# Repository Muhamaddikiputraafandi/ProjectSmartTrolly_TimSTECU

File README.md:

# Smart Shopping Trolley

Proyek ini bertujuan untuk mengembangkan Smart Shopping Trolley berbasis mikrokontroler yang dirancang untuk mempermudah pengalaman berbelanja di toko atau supermarket. Keranjang belanja ini dilengkapi dengan sensor RFID untuk membaca barang yang dimasukkan, menghitung total harga belanjaan secara otomatis, dan mengirimkan data pembelian ke aplikasi Android milik pembeli. 
Sistem ini menggunakan kombinasi teknologi barcode scanner, sensor RFID, dan komunikasi UART untuk memberikan solusi cerdas yang memungkinkan konsumen memantau total harga belanjaan secara real-time. Dengan konsep ini, konsumen tidak perlu lagi mengantri di kasir, sehingga proses checkout menjadi lebih cepat, efisien, dan nyaman.

## Fitur
- #### Barang Otomatis Terdeteksi :
    Setiap barang yang dimasukkan ke keranjang akan discan menggunakan barcode scanner atau RFID scanner.
- #### Perhitungan Otomatis Total Belanja :
    Setelah barang discan, sistem otomatis menambahkan harga barang ke total belanja.
- #### Koneksi Bluetooth UART ke Android :
    Total belanjaan, daftar barang, dan info lainnya dikirimkan secara real-time via modul Bluetooth (HC-05/HC-06) ke aplikasi Android.
- #### Manajemen Item :
    Di aplikasi Android, pengguna bisa Melihat daftar item belanja dan Menghapus item (fitur cancel jika batal beli barang).
- #### Notifikasi Suara/LED :
    LED indikator dan buzzer berbunyi jika terjadi event penting: Barang baru dimasukkan, Barang dibatalkan, dan Total harga berubah.
- #### Code Qris Pembayaran :
    Konsumen dapat melakukan pembayaran secara langsung melalui code Qris yang telah diinformasikan melalui gadget konsumen.

## Support By
- Dosen Pengampu : Akhmad Hendriawan ST., MT. (NIP.197501272002121003)
- Mata kuliah : Mikrokontroller
- Program Studi : D4 Teknik Elektronika
- Departemen Teknik Elektro
- Politeknik Elektronika Negeri Surabaya

## Team Member :

| NRP        | Nama                   | Jobdesk              | Akun        |
|------------|------------------------|----------------------|-------------|
| 2123600002 | Suci Tri Rahayu        |  Software Developer  | [Suci](https://github.com/sucirhyu)|
| 2123600008 | Samsul Ma'arif         |  Hardware Spesialist | [Samsul](https://github.com/samsul-21)|
| 2123600009 | M. Diki Putra Afandi   |  Project Manager     | [Diki](https://github.com/Muhamaddikiputraafandi)|
| 2123600012 | M. Daniel Prakusye     |  3D Designer         | [Daniel](https://github.com/danielwibowo)|
| 2123600016 | Ibrahim Fansori        |  PCB Designer        | [Ibrahim](https://github.com/IbrahimFansori)  |
| 2123600028 | M. Faqih Zulfikar      |  Software Developer  | [Faqih](https://github.com/faqihzulfi)|

## Preview Video Produk

📽️ [Tonton Video Produk](Dokumentasi/Video%20Promotion%20Product%20(1).mp4)

## 🛒 Cara Kerja Smart Trolley
1. Inisialisasi Aplikasi
•	Pengguna membuka aplikasi Smart Trolley.
•	Tersedia dua fitur utama: SCAN dan LIST.

2. Pemindaian Produk
•	Pengguna menekan tombol SCAN NOW untuk memulai pemindaian barcode/QR code produk.
•	Aplikasi mengaktifkan kamera dan membaca kode produk (misalnya: ITEM001).
•	Kode produk dikirim ke Arduino via Bluetooth (HC-06).

3. Pemrosesan di Arduino
•	Arduino menerima kode produk.
•	Mencocokkan kode dengan daftar item yang tersimpan di dalam memori (array).
•	Jika cocok:
    o	Tambahkan ke daftar belanja.
    o	Tampilkan nama & harga produk di OLED.
    o	Aktifkan buzzer sebagai konfirmasi.

4. Detail Produk di Aplikasi
•	Aplikasi menerima informasi barang (nama & harga) dari Arduino via Bluetooth.
•	Menampilkan detail produk.
•	User menekan “Add to Shopping List” → data tersimpan di daftar belanja aplikasi.

5. Daftar Belanja
•	Aplikasi menampilkan seluruh item yang telah dipindai.
•	Total harga ditampilkan secara otomatis.
•	Terdapat tombol Checkout untuk proses pembayaran.
•	(Opsional) User bisa membatalkan item tertentu → aplikasi kirim perintah BATAL ITEMxxx ke Arduino.

6. Pembayaran
•	Setelah checkout, aplikasi menampilkan kode QRIS untuk pembayaran menggunakan dompet digital.
•	User membayar menggunakan aplikasi pembayaran QRIS

7. Sukses Pembayaran
•	Setelah transaksi berhasil:
    o	Aplikasi menampilkan notifikasi "Payment Successful".
    o	Aplikasi mengirim sinyal ke Arduino:
            Menyalakan LED hijau.
            Mengaktifkan relay (misalnya membuka kunci troli/pintu loker sebagai tanda transaksi selesai).

## Foto 3D 

🔗 [Desain 3D Smart Trolley di Thingiverse](https://www.thingiverse.com/thing:7042336)

## Video Cara pembuatan 3D
📽️ [Tonton Video Panduan Desain 3D](https://intip.in/VIDEOPANDUANDESAIN3D)

## Demo Video Simulasi
🧪 [Klik di sini untuk melihat simulasi Wokwi](https://intip.in/simulasiwokwi)

## Design Figma
[Lihat Desain di Figma](https://www.figma.com/proto/pQICiX3LwqUT9YJWLTK00W/Smart-Trolley?node-id=0-1&t=6SqoGFO5Xu7j4LwM-1)

## Cara Kerja Apklikasi
[Tonton Video Penggunaan Apk](https://github.com/Muhamaddikiputraafandi/ProjectSmartTrolly_TimSTECU/blob/main/UI%20UX%20Design/Figma/Penggunaan%20Apk.mp4)

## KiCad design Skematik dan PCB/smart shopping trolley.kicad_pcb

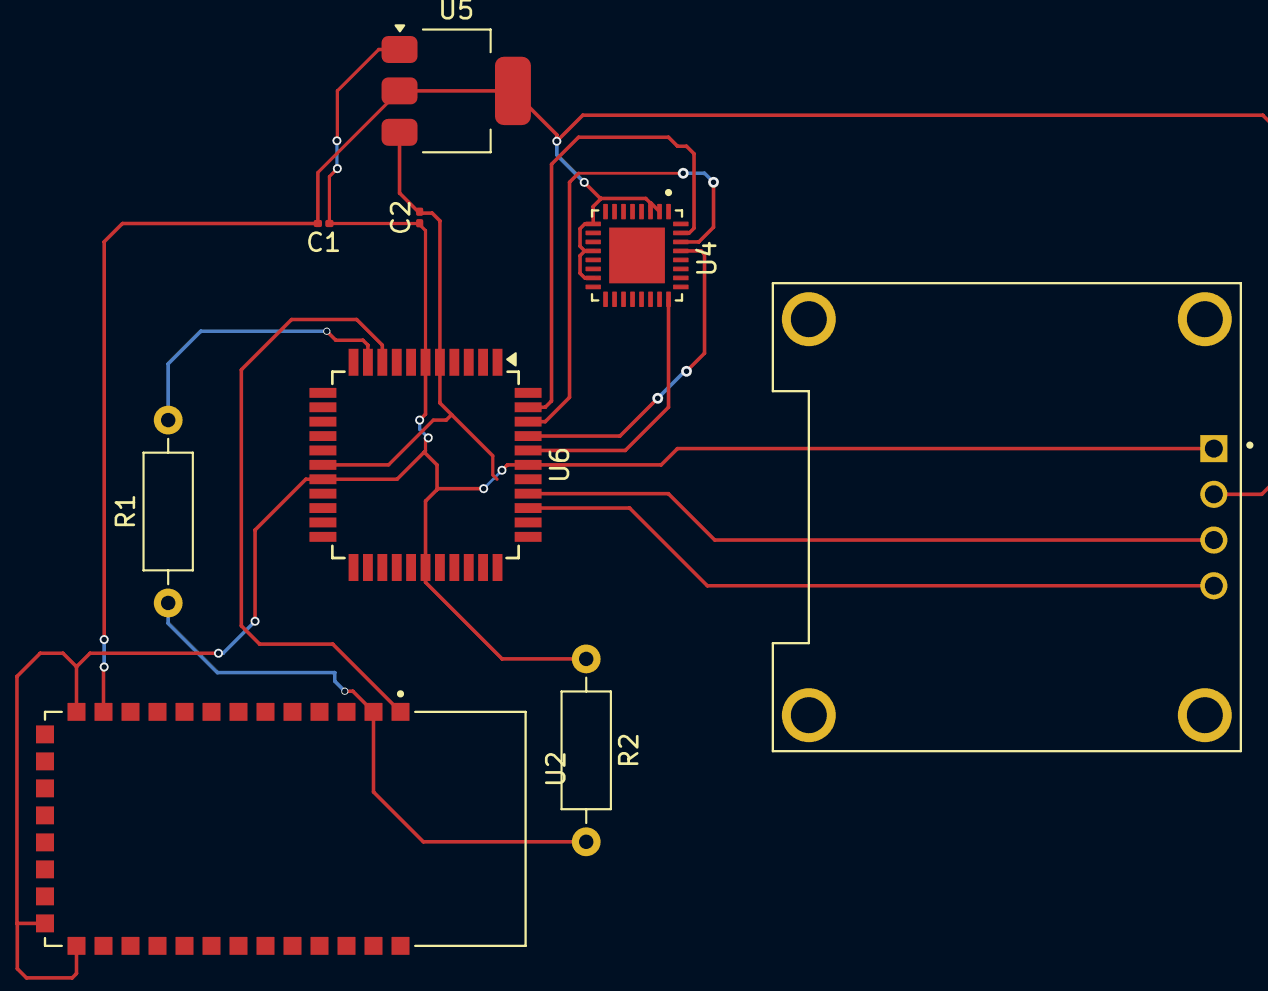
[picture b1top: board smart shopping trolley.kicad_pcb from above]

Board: 2 copper layers, 8 parts (0 on the bottom side), 10 nets.

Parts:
C1, C2: C_US; C_0201_0603Metric
R1: 1800; R_Axial_DIN0207_L6.3mm_D2.5mm_P10.16mm_Horizontal
R2: 3300; R_Axial_DIN0207_L6.3mm_D2.5mm_P10.16mm_Horizontal
U2: BLUETOOTH-SERIAL-HC-06; XCVR_BLUETOOTH-SERIAL-HC-06
U4: RC522; QFN50P500X500X100-33N
U5: AMS1117-3.3; SOT-223-3_TabPin2
U6: ATmega16A-A; TQFP-44_10x10mm_P0.8mm

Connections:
+3.3V: C1.2, U2.12 (3V3), U4.2 (PVDD), U4.3 (DVDD), U4.9 (SVDD), U4.12 (TVDD), U4.15 (AVDD), U5.2 (VO)
+5V: C2.2, U5.3 (VI), U6.5 (VCC), U6.17 (VCC), U6.38 (VCC)
unnamed: C1.1, C2.1, R2.1, U2.13 (GND), U2.21 (GND), U2.22 (GND), U5.1 (GND), U6.6 (GND), U6.18 (GND), U6.28 (GND), U6.39 (GND)
unnamed: R1.1, R2.2, U2.2 (RX)
unnamed: U2.1 (TX), U6.9 (PD0)
unnamed: U4.29 (D5/ADR_1/SCK/DTRQ), U6.41 (PB1)
unnamed: U4.30 (D6/ADR_0/MOSI/MX), U6.42 (PB2)
unnamed: U4.31 (D7/SCL/MISO/TX), U6.43 (PB3)
unnamed: U4.24 (SDA/NSS/RX), U6.40 (PB0)
unnamed: R1.2, U6.10 (PD1)

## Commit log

2025-04-28 Add File
2025-04-28 Update File
2025-04-30 Upload file .kicad_pcb dan .kicad_sch proyek Smart Trolley
    Menambahkan skematik dan layout PCB awal untuk proyek Smart Shopping Trolley berbasis ATmega16A.
2025-05-01 Add files via upload
    skematik smart trolly
2025-05-01 Add files via upload
    desain routing pcb
2025-05-05 Create file 1
    menambahakan folder
2025-05-05 Create file
    folder hardware
2025-05-05 Create file promotion
2025-05-05 Create simulasi
2025-05-11 Create skematik
2025-05-11 Create 1
2025-05-18 Create web design
2025-05-19 Thingiverse
    direct to uploaded file on thingiverse
2025-05-19 Create prototype
2025-05-19 Rename web design to design figma
2025-05-19 Rename 1 to File Blender Desain
2025-05-19 Create coba
2025-05-19 Rename 1 to Program Wokwi
2025-05-19 Rename 3d.jpg to 3D.jpg
2025-05-19 Rename pcb.png to PCB.png
2025-05-19 Rename scematic.pdf to Scematic.pdf
2025-05-19 Rename design figma to Design Figma
2025-05-19 Rename prototype to Produk Android
2025-05-19 Rename Produk Android to Produk UI UX
2025-05-19 Rename Program Sketch.IO to Program Sketch.ino
2025-05-19 Rename Video Promotion Product (1).mp4 to Video Promotion Product Smart Trolley.mp4
2025-05-19 Rename figma figma boy.pdf to Design UART to Android.pdf
2025-05-19 Rename Hardware/Diagram.Json to Hardware atau Simulasi
2025-05-19 Rename 3d.png to 3D.png
2025-05-19 Rename Produk UI UX to Produk UI UX (Proto Figma)
2025-05-19 Rename Design Figma to Design Figma UI UX
2025-05-19 Rename design pcb.pdf to Design PCB.pdf
2025-05-19 Rename pcb 2.pdf to PCB 2.pdf
2025-05-19 Rename pcb fix.png to PCB Fix.png
2025-05-19 Rename pcb kicad.pdf to PCB Kicad.pdf
2025-05-19 Rename pcb1.pdf to PCB1.pdf
2025-05-19 Update and rename smart shopping trolley.kicad_pcb to Smart Shopping Trolley Kicad_pcb
2025-05-19 Update and rename smart shopping trolley.kicad_sch to Smart Shopping Trolley Kicad_sch
2025-05-19 Create Video Panduan Desain 3D
2025-05-19 Update Video Panduan Desain 3D
2025-05-20 Create Simulasi wokwi
2025-05-30 Create Figma Design baru
2025-05-30 Create Simulate
2025-05-30 Update Simulate
2025-06-03 Create Video Simulasi
2025-06-03 Create TkinterWeb
2025-06-05 Create Panduan Bravo Studio
2025-06-05 Rename UI UX Design/Panduan penggunaan UART pada android.pdf to UI UX Design/Gui Python/Panduan penggunaan UART pada android.pdf
2025-06-05 Create Design Figma UI UX
2025-06-05 Rename UI UX Design/Design Figma UI UX to UI UX Design/Figma/Design Figma UI UX
2025-06-05 Rename UI UX Design/Design UART to Android.pdf to UI UX Design/Figma/Design UART to Android.pdf
2025-06-05 Rename UI UX Design/Figma Desain.pdf to UI UX Design/Figma/Figma Desain.pdf
2025-06-05 Rename UI UX Design/Produk UI UX (Proto Figma) to UI UX Design/Figma/Produk UI UX (Proto Figma)
2025-06-05 Create 1. Langkah Penggunaan Tkinter untuk UART
2025-06-05 Update 1. Langkah Penggunaan Tkinter untuk UART
2025-06-06 Create Alat Pendukung
2025-06-06 Update Design Figma UI UX
